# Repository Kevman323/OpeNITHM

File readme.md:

## WARNING: These PCBs are largely untested, and have been uploaded for reviewing, and initial orders. ORDER AT YOUR OWN RISK. There are no guarantees that it will work, or that these designs will be supported with a case in the future.
# BOARD VERSIONS:

Circut-Teensy32: Original small board for copper tape pads

Circut-Teensy32-Full-Board-upwards: Full PCB with upward firing WS2812 LEDs. JLC can assemble. - NOT TESTED

Circut-Teensy32-Full-Board-side: Full PCB with sideways firing SK6812 LEDs. JLC CANNOT assemble. - NOT TESTED

Circut-Teensy32-Full-Board-separate: Full PCB with slots cut for a separate LED board. There are no LEDs on the board itself. JLC can assemble. - NOT TESTED

Addon-LED-Board: Addon board for the above board. Has WS2812 LEDs, and slots into the main board for sideways firing. JLC PROBABLY can assemble, but only with the panelized version which combines 2 boards into one. - NOT TESTED

All boards have through hole spots for edge connectors, the teensy, the USB port, and the Barrel Jack. The separate LED board uses 1X3 90 angled 2.54 pitch connectors to attatch to the main board.

USB - USB4085-GF-A

Connectors - JST-PH. 9 pin for the Air boards, 4 pin for the air LEDs

Barrel Jack - any barrel jack with a standard 14x9mm footprint

Teensy LC - Make sure you connect the data lines on the teens before soldering to the board. You can either drop a pin straight down, or run wires out to the pads in front of it.

# OpeNITHM

This repository contails files related to OpeNITHM.

Firmware, schematics, board layout, and CAD files are included in this repo. Please see the CAD directory for the original 3d printed version, or the v2-cad directory for the laser cut version. 

## List of Hardware

In the `CAD\STL` folder, you will find numerous parts that must be 3D printed.

Please check out [the wiki](https://github.com/veroxzik/OpeNITHM/wiki/File-Explanation) for more information.

| Part | Qty |
| --- |:---:|
| Center Frame | 1 |
| Right Frame | 1 |
| Left Frame | 1 |
| Key Dual 2.5mm **OR** Key Dual 3mm<sup>1</sup> | 16 |
| LED Support Peg | 16 |
| Sensor Rail | 2 |
| Sensor Spacer Left<sup>2</sup> | 1 |
| Sensor Base Left<sup>2</sup> **OR** Integrated Sensor Base Left<sup>2</sup> | 1 |
| Sensor Cover Left<sup>2</sup> | 1 |
| Integrated Frame Mount Left<sup>2,3</sup> | 1 |

**NOTES:** 
1. Use 2.5mm for 3/32" and 3mm for 1/8" acrylic. 
2. Print out mirrored version of these parts as well.
3. Only print the frame mount if you are using the integrated sensor.

The non-printed materials and hardware include:

| Part                                                                       | Qty |
| --- |:---:|
| 4-40 Flat Head Screw, length 3/16" to 5/16" will work **OR** M3 equivalent | 2   |
| Top Acrylic Plate<sup>1</sup> (472mm x 112mm)                              | 1   |
| Key Acrylic<sup>1</sup> (103.5mm x 26mm)                                   | 16  |
| Copper Tape, cut into rectangles 95mm x 26mm                               | 16  |

**NOTES:**
1. Use 2.5mm (3/32") **OR** 3mm (1/8") acrylic. Use the same acrylic for top plate and keys.

## List of Electronics

OpeNITHM is designed for the Teensy LC.

#### Why use Teensy and not Arduino?

The biggest reason is that Teensy has built in capacitive sensing, which is how OpeNITHM fuctions. You have to fake it on Arduino using very controlled analog reads, and it is nowhere near as sensitive. In my (VXZK's) experience, it was simply impossible to use an Arduino to do the capacitive sensing required for this project.

I chose the Teensy LC as it is the lowest cost Teensy model available with capacitive sensing. The firmware and PCB are designed for this board alone; significant modifications may be required for any other version.

There is an alternative build using an Arduino Pro Micro and 2 MPR121s as a branch in this repo, but it is not maintained and not recommended. You're on your own with that one!

### Teensy LC Build

Links are mostly suggestions (except the Teensy, which is only officially available through the PJRC site and authorized resellers).  
(VXZK: I've heard a lot of trouble regarding good quality IR leds and phototransistors, so I've included specific links to the ones I purchased and has worked well for me.)  

The links below also assume you want to socket your Teensy and multiplexers for later use. You can solder them directly, if you'd like.  
If you are going to solder your sensors directly to the PCB, it is not necessary buy the 0.1" Pin Header, Right Angle. Otherwise, include female 0.1" sockets for your sensors (commonly referred to as Dupont connectors).  

| Part | Link | Qty |
| --- | --- |:---:|
| Teensy LC | https://www.pjrc.com/store/teensylc.html | 1 |
| Teensy LC Breakout Board | this Github, Circuit-Teensy32 folder contains gerbers | 1 |
| 74HC4051 Multiplexer Breakout Board | [Aliexpress][1] | 4 |
| 0.1" Pin Header, 1 row, 40 pos | [Aliexpress (qty 10)][2] | 2 |
| 0.1" Pin Header, Right Angle, 2 row, 24 pos | [LCSC][3] | 2 |
| 0.1" Socket, Straight, 1 row, 14 pos | [LCSC][4] | 2 |
| 0.1" Socket, Straight, 1 row, 5 pos | [LCSC][5] | 2 |
| 0.1" Socket, Straight, 1 row, 11 pos | [LCSC][6] | 2 |
| 0.1" Socket, Straight, 1 row, 8 pos | [LCSC][7] | 2 |
| 51k ohm Resistor, 1/6W or 1/8W | LCSC or Aliexpress | 6 |
| 33 ohm Resistor, 1/4W, 1/6W, or 1/8W | LCSC or Aliexpress | 3 |
| 1m WS2812B RGB 5V LED Strip, 30LED Per Meter | [Aliexpress][8] | 1 |
| IR LED and Phototransistor | [Ebay (Qty 20 pairs)][9] | 6 |

[1]: https://www.aliexpress.com/item/32807771098.html
[2]: https://www.aliexpress.com/item/665534073.html
[3]: https://lcsc.com/product-detail/New-Arrivals_XFCN-PZ254R-12-24P_C492440.html
[4]: https://lcsc.com/product-detail/Pin-Header-Female-Header_Boom-Precision-Elec-Female-header-2-54-1-14P_C52711.html
[5]: https://lcsc.com/product-detail/Pin-Header-Female-Header_Boom-Precision-Elec-2-54mm-1-5p-Female-header_C50950.html
[6]: https://lcsc.com/product-detail/Pin-Header-Female-Header_Changjiang-Connectors-A2541HWV-11P_C225508.html
[7]: https://lcsc.com/product-detail/Pin-Header-Female-Header_Boom-Precision-Elec-2-54mm-1-8P-Straight-Female-header_C27438.html
[8]: https://www.aliexpress.com/item/2036819167.html
[9]: https://www.ebay.com/itm/40pcs-5mm-Infrared-LED-940nm-Emitter-Diode-and-IR-Receiver-Set/252235145540

## Board Revision and Sensors

As of 2020-07-17, the recommended board version is v2.1, which features inputs for 32 sensors. This best replicates the feeling of the arcade. Previous versions used 16 sensors. If you still wish to make a 16 key version, you can order the v2.1 but only populate two of the multiplexers. This is not really recommended.

## Installing on Teensy LC

**NOTE:** This firmware is *only* written to work for the Teensy LC. Do *not* use Teensy 2.0 or Teensy 3.x

Skip this section if you are using a Pro Micro.

Locate your `arduino` folder (usually `C:\Program Files (x86)\arduino`).

#### I have a fresh install of Teensyduino, or have never modified my USB profiles

Copy `Firmware/Teensy/boards.txt` to `arduino\hardware\teensy\avr\` and overwrite the existing.

Copy `Firmware/Teensy/teensy3` to `arduino\hardware\teensy\avr\cores\teensy3` and overwrite any conflicts.

Copy `Firmware/FastLED/WS2812Serial.cpp` and `Firmware/FastLED/WS2812Serial.h` to `arduino\hardware\teensy\avr\libraries\WS2812Serial` and overwrite the existing.

Copy `Firmware/FastLED/FastLED.cpp` and `Firmware/FastLED/FastLED.h` to `[My Documents]\Arduino\libraries\FastLED\` and overwrite the existing.

#### I am applying the changes manually

(It is easier to copy and paste from the files in `Firmware/Teensy` instead of through here, the below is just for reference.)

Add `usb_nkro.c` and `usb_nkro.h` to `arduino\hardware\teensy\avr\cores\teensy3`

In `arduino\hardware\teesny\avr\boards.txt` add lines 1175-1179

```c
1175    teensyLC.menu.usb.nkrokeyboard=NKRO Keyboard
1176    teensyLC.menu.usb.nkrokeyboard.build.usbtype=USB_NKRO
1177    teensyLC.menu.usb.nkrokeyboard.fake_serial=teensy_gateway
1178    teensyLC.menu.usb.serialnkrokeyboard=Serial + NKRO Keyboard
1179    teensyLC.menu.usb.serialnkrokeyboard.build.usbtype=USB_SERIAL_NKRO

In `arduino\hardware\teensy\avr\cores\teensy3\WProgram.h` add line 59

```c
58    #include "usb_joystick.h"
59    #include "usb_nkro.h"
60    #include "usb_midi.h"
```

In `arduino\hardware\teensy\avr\cores\teensy3\usb_inst.cpp` add lines 75-77

```c
72    usb_serial_class Serial;
73    #endif
74    
75    #ifdef NKRO_INTERFACE
76    usb_nkro_class Nkro;
77    #endif
78    
79    #else // F_CPU < 20 MHz
```

In `arduino\hardware\teensy\avr\cores\teensy3\usb_dev.h` add lines 93-98

```c
90    extern volatile uint8_t keyboard_leds;
91    #endif
92    
93    #ifdef NKRO_INTERFACE
94    extern uint8_t nkro_report_data[NKRO_SIZE];
95    extern uint8_t nkro_protocol;
96    extern uint8_t nkro_idle_config;
97    extern uint8_t nkro_idle_count;
98    #endif
99    
100   #ifdef MIDI_INTERFACE
```

In `arduino\hardware\teensy\avr\cores\teensy3\usb_desc.h` add lines 868-948

```c
866      #define ENDPOINT15_CONFIG	ENDPOINT_TRANSMIT_ONLY
867    
868    #elif defined(USB_NKRO)
869      #define VENDOR_ID		0x16C0
870      #define PRODUCT_ID		0x04D0
871      #define MANUFACTURER_NAME	{'T','e','e','n','s','y','d','u','i','n','o'}
872      #define MANUFACTURER_NAME_LEN	11
873      #define PRODUCT_NAME		{'N','K','R','O',' ','K','e','y','b','o','a','r','d'}
874     #define PRODUCT_NAME_LEN	13
875      #define EP0_SIZE		64
876      #define NUM_ENDPOINTS         5
877      #define NUM_USB_BUFFERS	14
878      #define NUM_INTERFACE		4
879      #define SEREMU_INTERFACE      1	// Serial emulation
880      #define SEREMU_TX_ENDPOINT    1
881      #define SEREMU_TX_SIZE        64
882      #define SEREMU_TX_INTERVAL    1
883      #define SEREMU_RX_ENDPOINT    2
884      #define SEREMU_RX_SIZE        32
885      #define SEREMU_RX_INTERVAL    2
886      #define KEYBOARD_INTERFACE    0	// Keyboard
887      #define KEYBOARD_ENDPOINT     3
888      #define KEYBOARD_SIZE         8
889      #define KEYBOARD_INTERVAL     1
890      #define KEYMEDIA_INTERFACE    2	// Keyboard Media Keys
891      #define KEYMEDIA_ENDPOINT     4
892      #define KEYMEDIA_SIZE         8
893      #define KEYMEDIA_INTERVAL     4
894      #define NKRO_INTERFACE        3	// NKRO Keyboard
895      #define NKRO_ENDPOINT         5
896      #define NKRO_SIZE             32
897      #define NKRO_REPORT_KEYS		( NKRO_SIZE - 1 )
898      #define NKRO_INTERVAL         1
899      #define ENDPOINT1_CONFIG	ENDPOINT_TRANSMIT_ONLY
900      #define ENDPOINT2_CONFIG	ENDPOINT_RECEIVE_ONLY
901      #define ENDPOINT3_CONFIG	ENDPOINT_TRANSMIT_ONLY
902      #define ENDPOINT4_CONFIG	ENDPOINT_TRANSMIT_ONLY
903      #define ENDPOINT5_CONFIG	ENDPOINT_TRANSMIT_ONLY
904      #define ENDPOINT6_CONFIG	ENDPOINT_TRANSMIT_ONLY
905
906    #elif defined(USB_SERIAL_NKRO)
907      #define VENDOR_ID		0x16C0
908      #define PRODUCT_ID		0x0487
909      #define DEVICE_CLASS		0xEF
910      #define DEVICE_SUBCLASS	0x02
911      #define DEVICE_PROTOCOL	0x01
912      #define MANUFACTURER_NAME	{'T','e','e','n','s','y','d','u','i','n','o'}
913      #define MANUFACTURER_NAME_LEN	11
914      #define PRODUCT_NAME		{'S','e','r','i','a','l','/','N','K','R','O',' ','K','e','y','b','o','a','r','d'}
915      #define PRODUCT_NAME_LEN	20
916      #define EP0_SIZE		64
917      #define NUM_ENDPOINTS         6
918      #define NUM_USB_BUFFERS	14
919      #define NUM_INTERFACE		5
920      #define CDC_IAD_DESCRIPTOR	1
921      #define CDC_STATUS_INTERFACE	0
922      #define CDC_DATA_INTERFACE	1	// Serial
923      #define CDC_ACM_ENDPOINT	2
924      #define CDC_RX_ENDPOINT       3
925      #define CDC_TX_ENDPOINT       4
926      #define CDC_ACM_SIZE          16
927      #define CDC_RX_SIZE           64
928      #define CDC_TX_SIZE           64
929      #define KEYBOARD_INTERFACE    2	// Keyboard
930      #define KEYBOARD_ENDPOINT     1
931      #define KEYBOARD_SIZE         8
932      #define KEYBOARD_INTERVAL     1
933      #define KEYMEDIA_INTERFACE    3	// Keyboard Media Keys
934      #define KEYMEDIA_ENDPOINT     5
935      #define KEYMEDIA_SIZE         8
936      #define KEYMEDIA_INTERVAL     4
937      #define NKRO_INTERFACE        4	// NKRO Keyboard
938      #define NKRO_ENDPOINT         6
939      #define NKRO_SIZE             32
940      #define NKRO_REPORT_KEYS		( NKRO_SIZE - 1 )
941      #define NKRO_INTERVAL         1
942      #define ENDPOINT1_CONFIG	ENDPOINT_TRANSMIT_ONLY
943      #define ENDPOINT2_CONFIG	ENDPOINT_TRANSMIT_ONLY
944      #define ENDPOINT3_CONFIG	ENDPOINT_RECEIVE_ONLY
945      #define ENDPOINT4_CONFIG	ENDPOINT_TRANSMIT_ONLY
946      #define ENDPOINT5_CONFIG	ENDPOINT_TRANSMIT_ONLY
947      #define ENDPOINT6_CONFIG	ENDPOINT_TRANSMIT_ONLY
948    #endif
949    
950    #ifdef USB_DESC_LIST_DEFINE
```

In `arduino\hardware\teensy\avr\cores\teensy3\usb_desc.c` add lines 239-265

```c
236    };
237    #endif
238    
239    #ifdef NKRO_INTERFACE
240    // Via https://dawnmist.dreamwidth.org/1250.html
241    static uint8_t nkro_hid_report_desc[] = {
242            0x05, 0x01, // Usage Page (Generic Desktop),
243            0x09, 0x06, // Usage (Keyboard),
244            0xA1, 0x01, // Collection (Application),
245            // bitmap of modifiers
246            0x75, 0x01, // Report Size (1),
247            0x95, 0x08, // Report Count (8),
248            0x05, 0x07, // Usage Page (Key Codes),
249            0x19, 0xE0, // Usage Minimum (224),
250            0x29, 0xE7, // Usage Maximum (231),
251            0x15, 0x00, // Logical Minimum (0),
252            0x25, 0x01, // Logical Maximum (1),
253            0x81, 0x02, // Input (Data, Variable, Absolute), ;Modifier byte
254            // bitmap of keys
255            0x95, NKRO_REPORT_KEYS*8, // Report Count (),
256            0x75, 0x01, // Report Size (1),
257            0x15, 0x00, // Logical Minimum (0),
258            0x25, 0x01, // Logical Maximum(1),
259            0x05, 0x07, // Usage Page (Key Codes),
260            0x19, 0x00, // Usage Minimum (0),
261            0x29, NKRO_REPORT_KEYS*8-1, // Usage Maximum (),
262            0x81, 0x02, // Input (Data, Variable, Absolute),
263            0xc0 // End Collection
264    };
265    #endif
266    
267    #ifdef JOYSTICK_INTERFACE
268    #if JOYSTICK_SIZE == 12
```

In `arduino\hardware\teensy\avr\cores\teensy3\usb_desc.c` add lines 603-610 and modify line 612

```c
600    #define MULTITOUCH_INTERFACE_DESC_SIZE	0
601    #endif
602    
603    // Via https://dawnmist.dreamwidth.org/1250.html
604    #define NKRO_INTERFACE_DESC_POS	MULTITOUCH_INTERFACE_DESC_POS+MULTITOUCH_INTERFACE_DESC_SIZE
605    #ifdef  NKRO_INTERFACE
606    #define NKRO_INTERFACE_DESC_SIZE	9+9+7
607    #define NKRO_HID_DESC_OFFSET	NKRO_INTERFACE_DESC_POS+9
608    #else
609    #define NKRO_INTERFACE_DESC_SIZE	0
610    #endif
611    
612    #define CONFIG_DESC_SIZE		NKRO_INTERFACE_DESC_POS+NKRO_INTERFACE_DESC_SIZE
613    
614    
615    
616    // **************************************************************
```

In `arduino\hardware\teensy\avr\cores\teensy3\usb_desc.c` add lines 1131-1158

```c
1129   #endif // JOYSTICK_INTERFACE
1130   
1131   #ifdef NKRO_INTERFACE
1132           // interface descriptor, USB spec 9.6.5, page 267-269, Table 9-12
1133           9,                                      // bLength
1134           4,                                      // bDescriptorType
1135           NKRO_INTERFACE,                         // bInterfaceNumber
1136           0,                                      // bAlternateSetting
1137           1,                                      // bNumEndpoints
1138           0x03,                                   // bInterfaceClass (0x03 = HID)
1139           0x00,                                   // bInterfaceSubClass (0x01 = Boot)
1140           0x00,                                   // bInterfaceProtocol (0x01 = Keyboard)
1141           0,                                      // iInterface
1142           // HID interface descriptor, HID 1.11 spec, section 6.2.1
1143           9,                                      // bLength
1144           0x21,                                   // bDescriptorType
1145           0x11, 0x01,                             // bcdHID
1146           0,                                      // bCountryCode
1147           1,                                      // bNumDescriptors
1148           0x22,                                   // bDescriptorType
1149           LSB(sizeof(nkro_hid_report_desc)),      // wDescriptorLength
1150           MSB(sizeof(nkro_hid_report_desc)),
1151           // endpoint descriptor, USB spec 9.6.6, page 269-271, Table 9-13
1152           7,                                      // bLength
1153           5,                                      // bDescriptorType
1154           NKRO_ENDPOINT | 0x80,                   // bEndpointAddress
1155           0x03,                                   // bmAttributes (0x03=intr)
1156           NKRO_SIZE, 0,                           // wMaxPacketSize
1157           NKRO_INTERVAL,                          // bInterval
1158   #endif // NKRO_INTERFACE
1159   
1160   #ifdef MTP_INTERFACE
```

In `arduino\hardware\teensy\avr\cores\teensy3\usb_desc.c` add lines 1602-1605

```c
1600           {0x2100, MULTITOUCH_INTERFACE, config_descriptor+MULTITOUCH_HID_DESC_OFFSET, 9},
1601   #endif
1602   #ifdef NKRO_INTERFACE
1603           {0x2200, NKRO_INTERFACE, nkro_hid_report_desc, sizeof(nkro_hid_report_desc)},
1604           {0x2100, NKRO_INTERFACE, config_descriptor+NKRO_HID_DESC_OFFSET, 9},
1605   #endif
1606   #ifdef MTP_INTERFACE
```

In `arduino\hardware\teensy\avr\boards.txt` add lines 1175-1177
```
1174    teensyLC.menu.usb.flightsim.fake_serial=teensy_gateway
1175    teensyLC.menu.usb.nkrokeyboard=NKRO Keyboard
1176    teensyLC.menu.usb.nkrokeyboard.build.usbtype=USB_NKRO
1177    teensyLC.menu.usb.nkrokeyboard.fake_serial=teensy_gateway
1178    teensyLC.menu.usb.disable=No USB
```

## Configuring the Firmware and IDE

There are a number of options built into the firmware to give you flexibility in your implementation. These are presented as preprocessor defines that can be commented and uncommented to fit.

All user-editable defines are in `Config.h`, see the comments for additional information.

If you are not using either the Pro Micro or Teensy LC boards provided in this repo, it may be necessary to change the definitions of the pins, located in `PinConfig.h`.

If you do not have the FastLED and HID-Project libraries installed, do so though the `Tools->Manage Libraries` menu.

#### Compiling

When using a Pro Micro, select `Arduino/Genuino Micro` from `Tools->Board`.

When using a Teensy LC, select `Teensy LC` from `Tools->Board`, then select `NKRO Keyboard` from `Tools->USB Type` for reactive lights. If you are using serial light updates, select `Serial + NKRO Keyboard`.

Prior to compilation, review the (numerous) options available to the end user in `Config.h`. Comment and uncomment the corresponding options that match your setup.

## Running the Software

#### Configuring

To be revised.

#### Power On

To be revised.

#### Output

By default, the program will run in NKRO Keyboard mode. The specific keyboard keys are set in `USBOutput.cpp`, but are listed here in order of left to right:
```
a z s x d c f v g b h n j m k ,
```
When a second finger touches the pad, the following keys are pressed in order of left to right
```
1 q 2 w 3 e 4 r 5 t 6 y 7 u 8 i
```

By default, the air sensor functions as follows:
- `Home` is held as long as any sensor is triggered and released when there are no sensors triggered.
- `End` is pressed when any motion is detected, as long as the hand was previously in front of the sensors.
- `Page Up` is pressed and released when the sensor detections movement upwards.
- `Page Down` is pressed and released when the sensor detections movement downwards.

If `#define IR_SENSOR_KEY` is uncommented, each air sensor will report back individually. The default binding from bottom to top is:
```
/ . ' ; ] [
```
Per US QWERTY layout.

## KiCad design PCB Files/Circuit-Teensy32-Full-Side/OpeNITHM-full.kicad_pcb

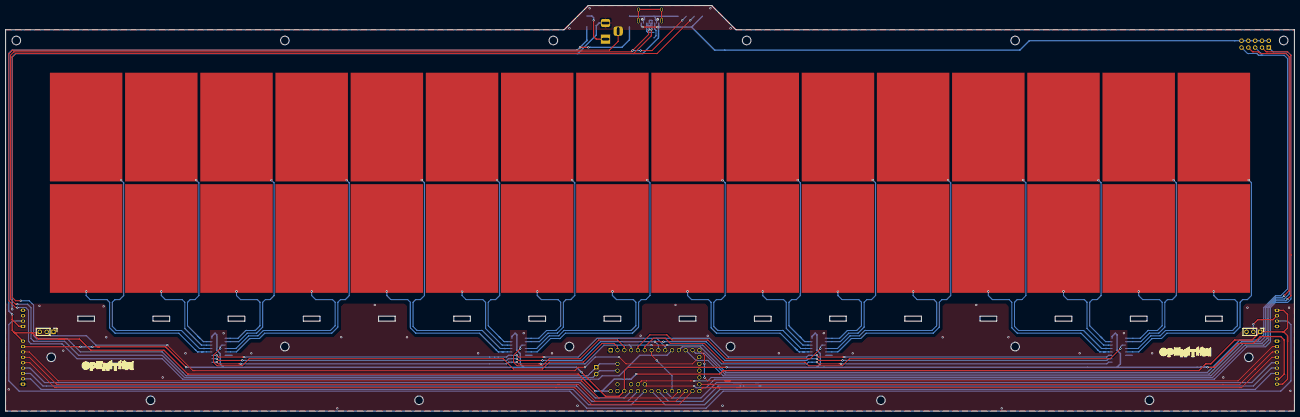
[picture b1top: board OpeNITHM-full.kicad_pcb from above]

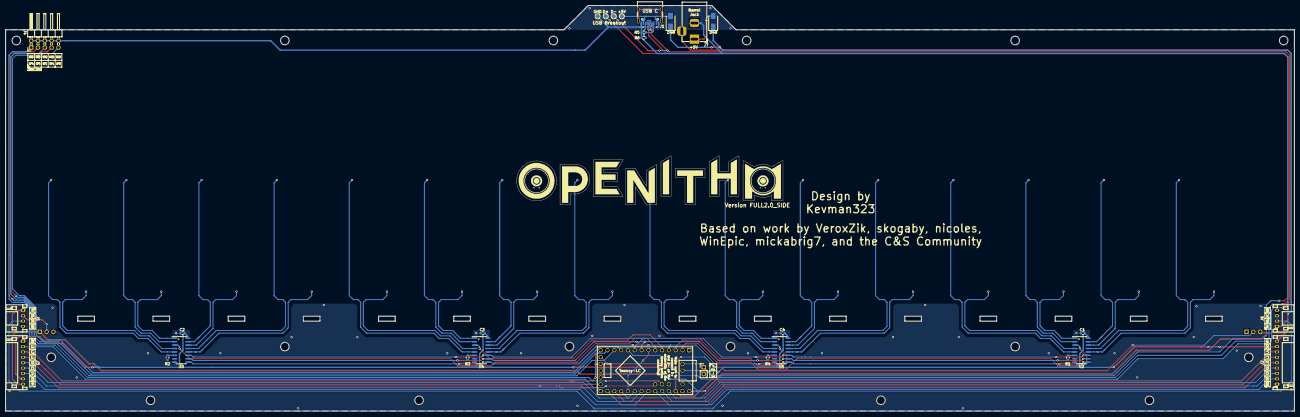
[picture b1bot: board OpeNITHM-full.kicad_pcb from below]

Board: 2 copper layers, 480.0 x 151.0 mm, 51 parts (30 on the bottom side), 74 nets.

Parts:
C1, C2, C3, C4: 100nF; C_0603_1608Metric
D48, D49: D_Schottky; D_SMA
H1, H2, H3, H4, H5, H6, H7, H8, H9, H10, H11, H12, H13, H14, H15, H16: MountingHole; MountingHole_3.2mm_M3_ISO14580
J1: USB_C_Receptacle; USB_C_Receptacle_HRO_TYPE-C-31-M-12
J2, J3: Conn_01x09; JST_PH_S9B-PH-K_1x09_P2.00mm_Horizontal
J4: Conn_02x05_Odd_Even; PinHeader_2x05_P2.54mm_Horizontal
J5, J6: Conn_01x04; JST_PH_S4B-PH-K_1x04_P2.00mm_Horizontal
J7: Barrel_Jack; BarrelJack_Horizontal
J8: Conn_01x02; PinHeader_1x02_P2.54mm_Vertical
J9, J10: Conn_01x03; PinHeader_1x03_P2.54mm_Vertical
Keys1: Conn_02x16_Odd_Even; Pads
LOGO1, LOGO3: Logo; openithm-logo
LOGO2: Logo; openithm-big
R1, R2, R3, R4: 10k; R_0603_1608Metric
R5, R6: 5.1k; R_0603_1608Metric
TP1: +5V; TestPoint_Pad_D1.5mm
TP2: D-; TestPoint_Pad_D1.5mm
TP3: D+; TestPoint_Pad_D1.5mm
TP4: GND; TestPoint_Pad_D1.5mm
U1: Teensy-LC; TeensyLC
U2, U3, U4, U5: 74HC4051D; SOIC-16_3.9x9.9mm_P1.27mm

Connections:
+3V3: C1.2, C2.2, C3.2, C4.2, J2.8, J3.8, U1.31, U2.16, U3.16, U4.16, U5.16
+5V: D48.1, D49.1, J2.9, J3.9, J5.1, J6.1, J9.3, J10.1, U1.33
/AIR_LED_0: J2.5, U1.21
/AIR_LED_1: J3.4, U1.20
/AIR_LED_2: J2.6, U1.22
/AIR_LED_3: J3.3, U1.19
/AIR_LED_4: J2.7, U1.23
/AIR_LED_5: J3.2, U1.14
/AIR_SENSOR_0: J3.5, U1.25
/AIR_SENSOR_1: J2.4, U1.30
/AIR_SENSOR_2: J3.6, U1.26
/AIR_SENSOR_3: J2.3, U1.29
/AIR_SENSOR_4: J3.7, U1.27
/AIR_SENSOR_5: J2.2, U1.28
/BARREL_DETECT: J7.3, U1.10
/KEY_0: Keys1.1, U2.13
/KEY_1: Keys1.3, U2.15
/KEY_2: Keys1.5, U2.2
/KEY_3: Keys1.7, U2.5
/KEY_4: Keys1.9, U5.13
/KEY_5: Keys1.11, U5.15
/KEY_6: Keys1.13, U5.2
/KEY_7: Keys1.15, U5.5
/KEY_8: Keys1.2, U2.12
/KEY_9: Keys1.4, U2.14
/KEY_10: Keys1.6, U2.1
/KEY_11: Keys1.8, U2.4
/KEY_12: Keys1.10, U5.12
/KEY_13: Keys1.12, U5.14
/KEY_14: Keys1.14, U5.1
/KEY_15: Keys1.16, U5.4
/KEY_16: Keys1.17, U4.13
/KEY_17: Keys1.19, U4.15
/KEY_18: Keys1.21, U4.2
/KEY_19: Keys1.23, U4.5
/KEY_20: Keys1.25, U3.13
/KEY_21: Keys1.27, U3.15
/KEY_22: Keys1.29, U3.2
/KEY_23: Keys1.31, U3.5
/KEY_24: Keys1.18, U4.12
/KEY_25: Keys1.20, U4.14
/KEY_26: Keys1.22, U4.1
/KEY_27: Keys1.24, U4.4
/KEY_28: Keys1.26, U3.12
/KEY_29: Keys1.28, U3.14
/KEY_30: Keys1.30, U3.1
/KEY_31: Keys1.32, U3.4
/KEY_LED/DO: J5.2, J10.2
/MUX_0: U1.9, U2.11, U3.11, U4.11, U5.11
/MUX_1: U1.8, U2.10, U3.10, U4.10, U5.10
/MUX_2: U1.4, U2.9, U3.9, U4.9, U5.9
/RGB_DO: U1.7, U1.24
/RGB_DO_BUF: J9.2, U1.15
/SPARE_0: J4.9, U1.11
/SPARE_1: J4.7, U1.13
/SPARE_2: J4.5, U1.12
/SPARE_3: J4.3, U1.36
/SPARE_4: J4.1, U1.37
/TOUCH_0: U1.2, U2.3
/TOUCH_1: U1.6, U3.3
/TOUCH_2: U1.5, U4.3
/TOUCH_3: U1.3, U5.3
/USB_D+: J1.A6, J1.B6, J8.1, TP3.1, U1.38
/USB_D-: J1.A7, J1.B7, J8.2, TP2.1, U1.39
GND: C1.1, C2.1, C3.1, C4.1, J1.A1, J1.A12, J1.B1, J1.B12, J2.1, J3.1, J4.2, J4.4, J4.6, J4.8, J4.10, J5.4, J6.4, J7.2, J9.1, J10.3, R1.2, R2.2, R3.2, R4.2, R5.1, R6.1, TP4.1, U1.1, U1.32, U2.7, U2.8, U3.7, U3.8, U4.7, U4.8, U5.7, U5.8
unnamed: D48.2, J1.A4, J1.A9, J1.B4, J1.B9, TP1.1
unnamed: D49.2, J7.1
unnamed: J1.A5, R5.2
unnamed: J1.B5, R6.2
unnamed: J5.3, J6.2
unnamed: R1.1, U2.6
unnamed: R2.1, U3.6
unnamed: R3.1, U4.6
unnamed: R4.1, U5.6

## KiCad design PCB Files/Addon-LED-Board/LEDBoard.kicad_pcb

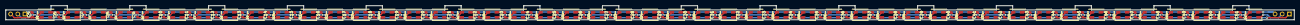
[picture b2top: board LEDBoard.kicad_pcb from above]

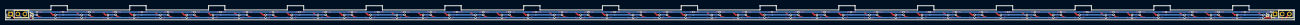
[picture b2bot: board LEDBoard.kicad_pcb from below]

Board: 2 copper layers, 458.0 x 5.0 mm, 96 parts (2 on the bottom side), 34 nets.

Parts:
C5, C6, C7, C8, C9, C10, C11, C12, C13, C14, C15, C16, C17, C18, C19, C20, C21, C22, C23, C24, C25, C26, C27, C28, C29, C30, C31, C32, C33, C34, C35, C36, C37, C38, C39, C40, C41, C42, C43, C44, C45, C46, C47, C48, C49, C50, C51: 100nF; C_0603_1608Metric
D1, D2, D3, D4, D5, D6, D7, D8, D9, D10, D11, D12, D13, D14, D15, D16, D17, D18, D19, D20, D21, D22, D23, D24, D25, D26, D27, D28, D29, D30, D31, D32, D33, D34, D35, D36, D37, D38, D39, D40, D41, D42, D43, D44, D45, D46, D47: WS2812B-MINI; LED_WS2812B-MINI_LED-4_3535_3.5x3.5mm
J1, J2: Conn_01x03; PinHeader_1x03_P2.54mm_Vertical

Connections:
+5V: C5.2, C6.2, C7.2, C8.2, C9.2, C10.2, C11.2, C12.2, C13.2, C14.2, C15.2, C16.2, C17.2, C18.2, C19.2, C20.2, C21.2, C22.2, C23.2, C24.2, C25.2, C26.2, C27.2, C28.2, C29.2, C30.2, C31.2, C32.2, C33.2, C34.2, C35.2, C36.2, C37.2, C38.2, C39.2, C40.2, C41.2, C42.2, C43.2, C44.2, C45.2, C46.2, C47.2, C48.2, C49.2, C50.2, C51.2, D1.2, D2.2, D3.2, D4.2, D5.2, D6.2, D7.2, D8.2, D9.2, D10.2, D11.2, D12.2, D13.2, D14.2, D15.2, D16.2, D17.2, D18.2, D19.2, D20.2, D21.2, D22.2, D23.2, D24.2, D25.2, D26.2, D27.2, D28.2, D29.2, D30.2, D31.2, D32.2, D33.2, D34.2, D35.2, D36.2, D37.2, D38.2, D39.2, D40.2, D41.2, D42.2, D43.2, D44.2, D45.2, D46.2, D47.2, J1.3, J2.1
/DI: D1.1, D2.1, J1.2
/DO: D47.3, J2.2
GND: C5.1, C6.1, C7.1, C8.1, C9.1, C10.1, C11.1, C12.1, C13.1, C14.1, C15.1, C16.1, C17.1, C18.1, C19.1, C20.1, C21.1, C22.1, C23.1, C24.1, C25.1, C26.1, C27.1, C28.1, C29.1, C30.1, C31.1, C32.1, C33.1, C34.1, C35.1, C36.1, C37.1, C38.1, C39.1, C40.1, C41.1, C42.1, C43.1, C44.1, C45.1, C46.1, C47.1, C48.1, C49.1, C50.1, C51.1, D1.4, D2.4, D3.4, D4.4, D5.4, D6.4, D7.4, D8.4, D9.4, D10.4, D11.4, D12.4, D13.4, D14.4, D15.4, D16.4, D17.4, D18.4, D19.4, D20.4, D21.4, D22.4, D23.4, D24.4, D25.4, D26.4, D27.4, D28.4, D29.4, D30.4, D31.4, D32.4, D33.4, D34.4, D35.4, D36.4, D37.4, D38.4, D39.4, D40.4, D41.4, D42.4, D43.4, D44.4, D45.4, D46.4, D47.4, J1.1, J2.3
unnamed: D2.3, D3.1
unnamed: D3.3, D4.1, D5.1
unnamed: D5.3, D6.1
unnamed: D6.3, D7.1, D8.1
unnamed: D8.3, D9.1
unnamed: D9.3, D10.1, D11.1
unnamed: D11.3, D12.1
unnamed: D12.3, D13.1, D14.1
unnamed: D14.3, D15.1
unnamed: D15.3, D16.1, D17.1
unnamed: D17.3, D18.1
unnamed: D18.3, D19.1, D20.1
unnamed: D20.3, D21.1
unnamed: D21.3, D22.1, D23.1
unnamed: D23.3, D24.1
unnamed: D24.3, D25.1, D26.1
unnamed: D26.3, D27.1
unnamed: D27.3, D28.1, D29.1
unnamed: D29.3, D30.1
unnamed: D30.3, D31.1, D32.1
unnamed: D32.3, D33.1
unnamed: D33.3, D34.1, D35.1
unnamed: D35.3, D36.1
unnamed: D36.3, D37.1, D38.1
unnamed: D38.3, D39.1
unnamed: D39.3, D40.1, D41.1
unnamed: D41.3, D42.1
unnamed: D42.3, D43.1, D44.1
unnamed: D44.3, D45.1
unnamed: D45.3, D46.1, D47.1

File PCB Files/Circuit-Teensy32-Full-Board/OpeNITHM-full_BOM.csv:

Comment,Designator,Footprint,LCSC
100nF,"C1,C2,C3,C4,C5,C6,C7,C8,C9,C10,C11,C12,C13,C14,C15,C16,C17,C18,C19,C20,C21,C22,C23,C24,C25,C26,C27,C28,C29,C30,C31,C32,C33,C34,C35",Capacitor_SMD:C_0603_1608Metric,C14663
WS2812B-B,"D1,D2,D3,D4,D5,D6,D7,D8,D9,D10,D11,D12,D13,D14,D15,D16,D17,D18,D19,D20,D21,D22,D23,D24,D25,D26,D27,D28,D29,D30,D31",LED_SMD:LED_WS2812B_PLCC4_5.0x5.0mm_P3.2mm,C114586
10k,"R1,R2,R3,R4",Resistor_SMD:R_0603_1608Metric,C25804
74HC4051D,"U2,U3,U4,U5",Package_SO:SOIC-16_3.9x9.9mm_P1.27mm,C9386

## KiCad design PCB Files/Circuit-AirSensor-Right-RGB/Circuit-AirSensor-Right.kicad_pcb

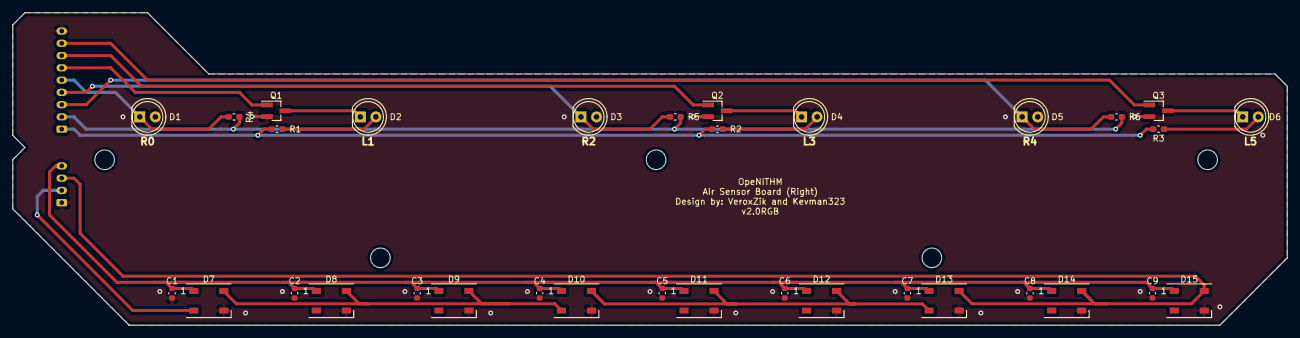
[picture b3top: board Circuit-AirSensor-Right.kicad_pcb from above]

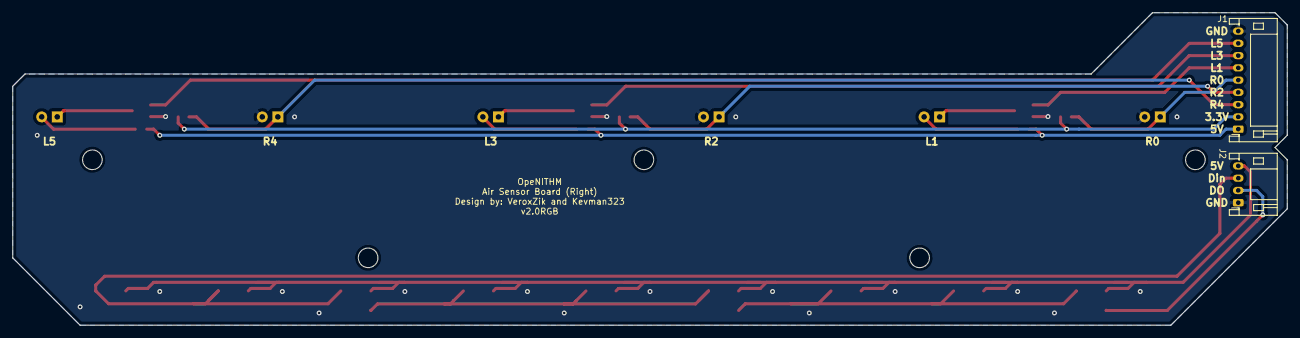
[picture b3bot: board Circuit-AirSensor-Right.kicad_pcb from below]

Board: 2 copper layers, 208.0 x 51.0 mm, 40 parts (2 on the bottom side), 20 nets.

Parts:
C1, C2, C3, C4, C5, C6, C7, C8, C9: 100nF; C_0603_1608Metric
D1, D3, D5: IR Photodiode; LED_D5.0mm
D2, D4, D6: IR LED; LED_D5.0mm
D7, D8, D9, D10, D11, D12, D13, D14, D15: WS2812B; LED_WS2812B_PLCC4_5.0x5.0mm_P3.2mm
J1: JST PH R/A; JST_PH_S9B-PH-K_1x09_P2.00mm_Horizontal
J2: Conn_01x04; JST_PH_S4B-PH-K_1x04_P2.00mm_Horizontal
MH1, MH2, MH3, MH4, MH5: MountingHole; MountingHole_3.2mm_M3_ISO14580
Q1, Q2, Q3: 2N7002; SOT-23_Handsoldering
R1, R2, R3: 82; R_0603_1608Metric_Pad1.05x0.95mm_HandSolder
R4, R5, R6: 10k; R_0603_1608Metric_Pad1.05x0.95mm_HandSolder

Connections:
+3V3: J1.2, R4.1, R5.1, R6.1
+5V: J1.1, R1.1, R2.1, R3.1
DO: D7.2, J2.2
Din: D13.4, D14.4, D15.4, J2.3
GND: C1.2, C2.2, C3.2, C4.2, C5.2, C6.2, C7.2, C8.2, C9.2, D1.2, D3.2, D5.2, D7.3, D8.3, D9.3, D10.3, D11.3, D12.3, D13.3, D14.3, D15.3, J1.9, J2.1, Q1.2, Q2.2, Q3.2
L1: J1.6, Q1.1
L3: J1.7, Q2.1
L5: J1.8, Q3.1
unnamed: D2.1, Q1.3
unnamed: D2.2, R1.2
unnamed: D4.1, Q2.3
unnamed: D4.2, R2.2
unnamed: D6.1, Q3.3
unnamed: D6.2, R3.2
unnamed: D7.4, D8.4, D9.4, D10.2
unnamed: D10.4, D11.4, D12.4, D13.2
R0: D1.1, J1.5, R4.2
R2: D3.1, J1.4, R5.2
R4: D5.1, J1.3, R6.2
RGB+5V: C1.1, C2.1, C3.1, C4.1, C5.1, C6.1, C7.1, C8.1, C9.1, D7.1, D8.1, D9.1, D10.1, D11.1, D12.1, D13.1, D14.1, D15.1, J2.4

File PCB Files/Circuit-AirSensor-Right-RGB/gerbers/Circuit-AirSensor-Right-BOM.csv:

Comment,Designator,Footprint,LCSC
"100nF","C1,C2,C3,C4,C5,C6,C7,C8,C9","Capacitor_SMD:C_0603_1608Metric","C14663"
"IR Photodiode","D1,D3,D5","AirSensor_Local:LED_D5.0mm",""
"IR LED","D2,D4,D6","AirSensor_Local:LED_D5.0mm",""
"WS2812B","D7,D8,D9,D10,D11,D12,D13,D14,D15","LED_SMD:LED_WS2812B_PLCC4_5.0x5.0mm_P3.2mm",""
"JST PH R/A","J1","Connector_JST:JST_PH_S9B-PH-K_1x09_P2.00mm_Horizontal",""
"Conn_01x04","J2","Connector_JST:JST_PH_S4B-PH-K_1x04_P2.00mm_Horizontal",""
"MountingHole","MH1,MH2,MH3,MH4,MH5","MountingHole:MountingHole_3.2mm_M3_ISO14580",""
"2N7002","Q1,Q2,Q3","Package_TO_SOT_SMD:SOT-23_Handsoldering","C8545"
"82","R1,R2,R3","Resistor_SMD:R_0603_1608Metric_Pad1.05x0.95mm_HandSolder"," C23255"
"10k","R4,R5,R6","Resistor_SMD:R_0603_1608Metric_Pad1.05x0.95mm_HandSolder","C25804"

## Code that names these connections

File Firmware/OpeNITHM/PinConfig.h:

#include "Config.h"

#ifndef _PINCONFIG_h
#define _PINCONFIG_h

// Multiplexer pin settings
#if defined(OPENITHM_V1_0)
#define MUX_0 20
#define MUX_1 19
#define MUX_2 18
#elif defined(OPENITHM_V1_1)
#define MUX_0 2
#define MUX_1 1
#define MUX_2 0
#elif defined(OPENITHM_V2_0)
#define MUX_0 0
#define MUX_1 1
#define MUX_2 2
#elif defined(OPENITHM_V2_1)
#define MUX_0 2
#define MUX_1 3
#define MUX_2 4
#elif defined(OPENITHM_FULL_V1_0)
#define MUX_0 4
#define MUX_1 3
#define MUX_2 2
#elif defined(OPENITHM_FULL2_0_SIDE) || defined(OPENITHM_FULL2_0_UP)
#define MUX_0 7
#define MUX_1 6
#define MUX_2 2
#endif

// Sensor pin settings
#if defined(OPENITHM_V1_0)
#define LED_0 16
#define LED_1 21
#define LED_2 5
#elif defined(OPENITHM_V1_1) || defined(OPENITHM_V2_0)
#define LED_0 7
#define LED_1 6
#define LED_2 5
#elif defined(OPENITHM_V2_1) || defined(OPENITHM_FULL_V1_0)
#define LED_0 8
#define LED_1 7
#define LED_2 6
#elif defined(OPENITHM_FULL2_0_SIDE) || defined(OPENITHM_FULL2_0_UP)
#define LED_0 14
#define LED_1 13
#define LED_2 15
#define LED_3 26
#define LED_4 16
#define LED_5 12
#endif

#ifdef IR_SENSOR_MULTIPLEXED
#define SENSOR_IN A0
#else
#if defined(OPENITHM_V1_0)
#define AIR_SENSOR_0_PIN 10
#define AIR_SENSOR_1_PIN 11
#define AIR_SENSOR_2_PIN 12
#define AIR_SENSOR_3_PIN 6
#define AIR_SENSOR_4_PIN 8
#define AIR_SENSOR_5_PIN 9
#elif defined(OPENITHM_V1_1)
#define AIR_SENSOR_0_PIN 20
#define AIR_SENSOR_1_PIN 19
#define AIR_SENSOR_2_PIN 18
#define AIR_SENSOR_3_PIN 23
#define AIR_SENSOR_4_PIN 22
#define AIR_SENSOR_5_PIN 21
#elif defined(OPENITHM_V2_0) || defined(OPENITHM_V2_1) || defined(OPENITHM_FULL_V1_0)
#define AIR_SENSOR_0_PIN 18
#define AIR_SENSOR_1_PIN 20
#define AIR_SENSOR_2_PIN 22
#define AIR_SENSOR_3_PIN 19
#define AIR_SENSOR_4_PIN 21
#define AIR_SENSOR_5_PIN 23
#elif defined(OPENITHM_FULL2_0_SIDE) || defined(OPENITHM_FULL2_0_UP)
#define AIR_SENSOR_0_PIN 18
#define AIR_SENSOR_1_PIN 23
#define AIR_SENSOR_2_PIN 19
#define AIR_SENSOR_3_PIN 22
#define AIR_SENSOR_4_PIN 20
#define AIR_SENSOR_5_PIN 21
#endif
#endif

// Capsense pin settings
#if defined(OPENITHM_V1_0)
#define TOUCH_0 22
#define TOUCH_1 23
#elif defined(OPENITHM_V1_1)
#define TOUCH_0 16
#define TOUCH_1 3
#elif defined(OPENITHM_V2_0)
#define TOUCH_0 16
#define TOUCH_1 3
#define TOUCH_2 4
#define TOUCH_3 15
#elif defined(OPENITHM_V2_1)
#define TOUCH_0 16
#define TOUCH_1 0
#define TOUCH_2 1
#define TOUCH_3 15
#elif defined(OPENITHM_FULL_V1_0)
#define TOUCH_0 1
#define TOUCH_1 15
#define TOUCH_2 16
#define TOUCH_3 0
#elif defined(OPENITHM_FULL2_0_SIDE) || defined(OPENITHM_FULL2_0_UP)
#define TOUCH_0 0
#define TOUCH_1 4
#define TOUCH_2 3
#define TOUCH_3 1
#endif

// Lighting pin settings
#ifdef USE_DMA_RGB
  #define LED_TYPE    WS2812SERIAL
  #define LED_ORDER   BRG
#else
  #define LED_TYPE    WS2812B
  #define LED_ORDER   GRB
#endif

#if defined(OPENITHM_V1_0)
  #define RGBPIN 4
#elif defined(OPENITHM_V1_1) || defined(OPENITHM_V2_0)
    #ifdef USE_DMA_RGB
       #define RGBPIN 24
    #else
       #define RGBPIN 11
    #endif
#elif defined(OPENITHM_V2_1) || defined(OPENITHM_FULL_V1_0) || defined(OPENITHM_FULL2_0_SIDE) || defined(OPENITHM_FULL2_0_UP)
  #define RGBPIN 5
#endif

#endif  // _PINCONFIG_h

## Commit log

2020-12-28 Full PCB V1. I messed up github, so this is a re-upload
2021-01-31 Update readme to reflect status of the full board
2021-02-15 Preliminary upload of the Fullboard v2.0 PCB, and it's separate LED board. Nothing here should be purchased, this is just uploaded for reviewing.
2021-02-18 Separate Upwards Firing, and Side Firing PCBs, still both untested. 3rd Addon LED Board version coming later.
2021-02-18 Fix Side Board Gerbers
2021-02-18 damn it, fixed...
2021-02-19 Minor trace edit. Has no impact on board function
2021-02-19 Add PCB with separate addon board for side firing
2021-02-19 Update readme to reflect different board versions, and provide some info
2021-02-19 wrong bold
2021-02-19 I'll get this right eventually
2021-02-23 Fixed addon LED board. Previous version will not work, pins were wrong
2021-02-27 Minor silkscreen fix
2021-03-01 LARGE BOARD CHANGES Folders for all boards changed
    Side Firing board: Removed due to lack of interest. Go back a commit to get it. It should be fully functional, just not supported.
    Upwards Firing Board:
    USBc Port moved to the top of the board for JLC assembly
    Adjusted Credits
    Added unique version number
    Addon Board: Now Called Side Board:
2021-03-01 Rename BOM file and fix chip rotations for JLC
2021-03-17 More big board firmware changes
2021-03-17 Fix key arrays. I got them backwards PLUS messed up the other board version.
2021-03-22 Add RGB Air tower PCB. These are untested.
2021-03-24 Renamed RGB air board folders
2021-03-24 Widened slots on side firing board
2021-03-26 fix assembly file
